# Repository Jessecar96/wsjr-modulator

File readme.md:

# The Weather STAR Revamped

This project is an update to https://github.com/thetechknight/wsjr-modulator that replaces the Arduino Mega, with a Reaspberry Pi Zero. This allows you to write a data sending solution on device instead of requiring a connection to another computer or server for data.

The `schematic` folder contains the updated schematic and board layout files in KiCad 8. 
`schematic_orig` contains thetechknight's original EAGLE cad schematic.
`code` contains code written for the Arduino based board written for  BASCOM-AVR.

The software that runs on the Raspberry Pi can be found here: https://github.com/Jessecar96/wsjr-data-encoder

License: https://creativecommons.org/licenses/by-nc-sa/4.0/

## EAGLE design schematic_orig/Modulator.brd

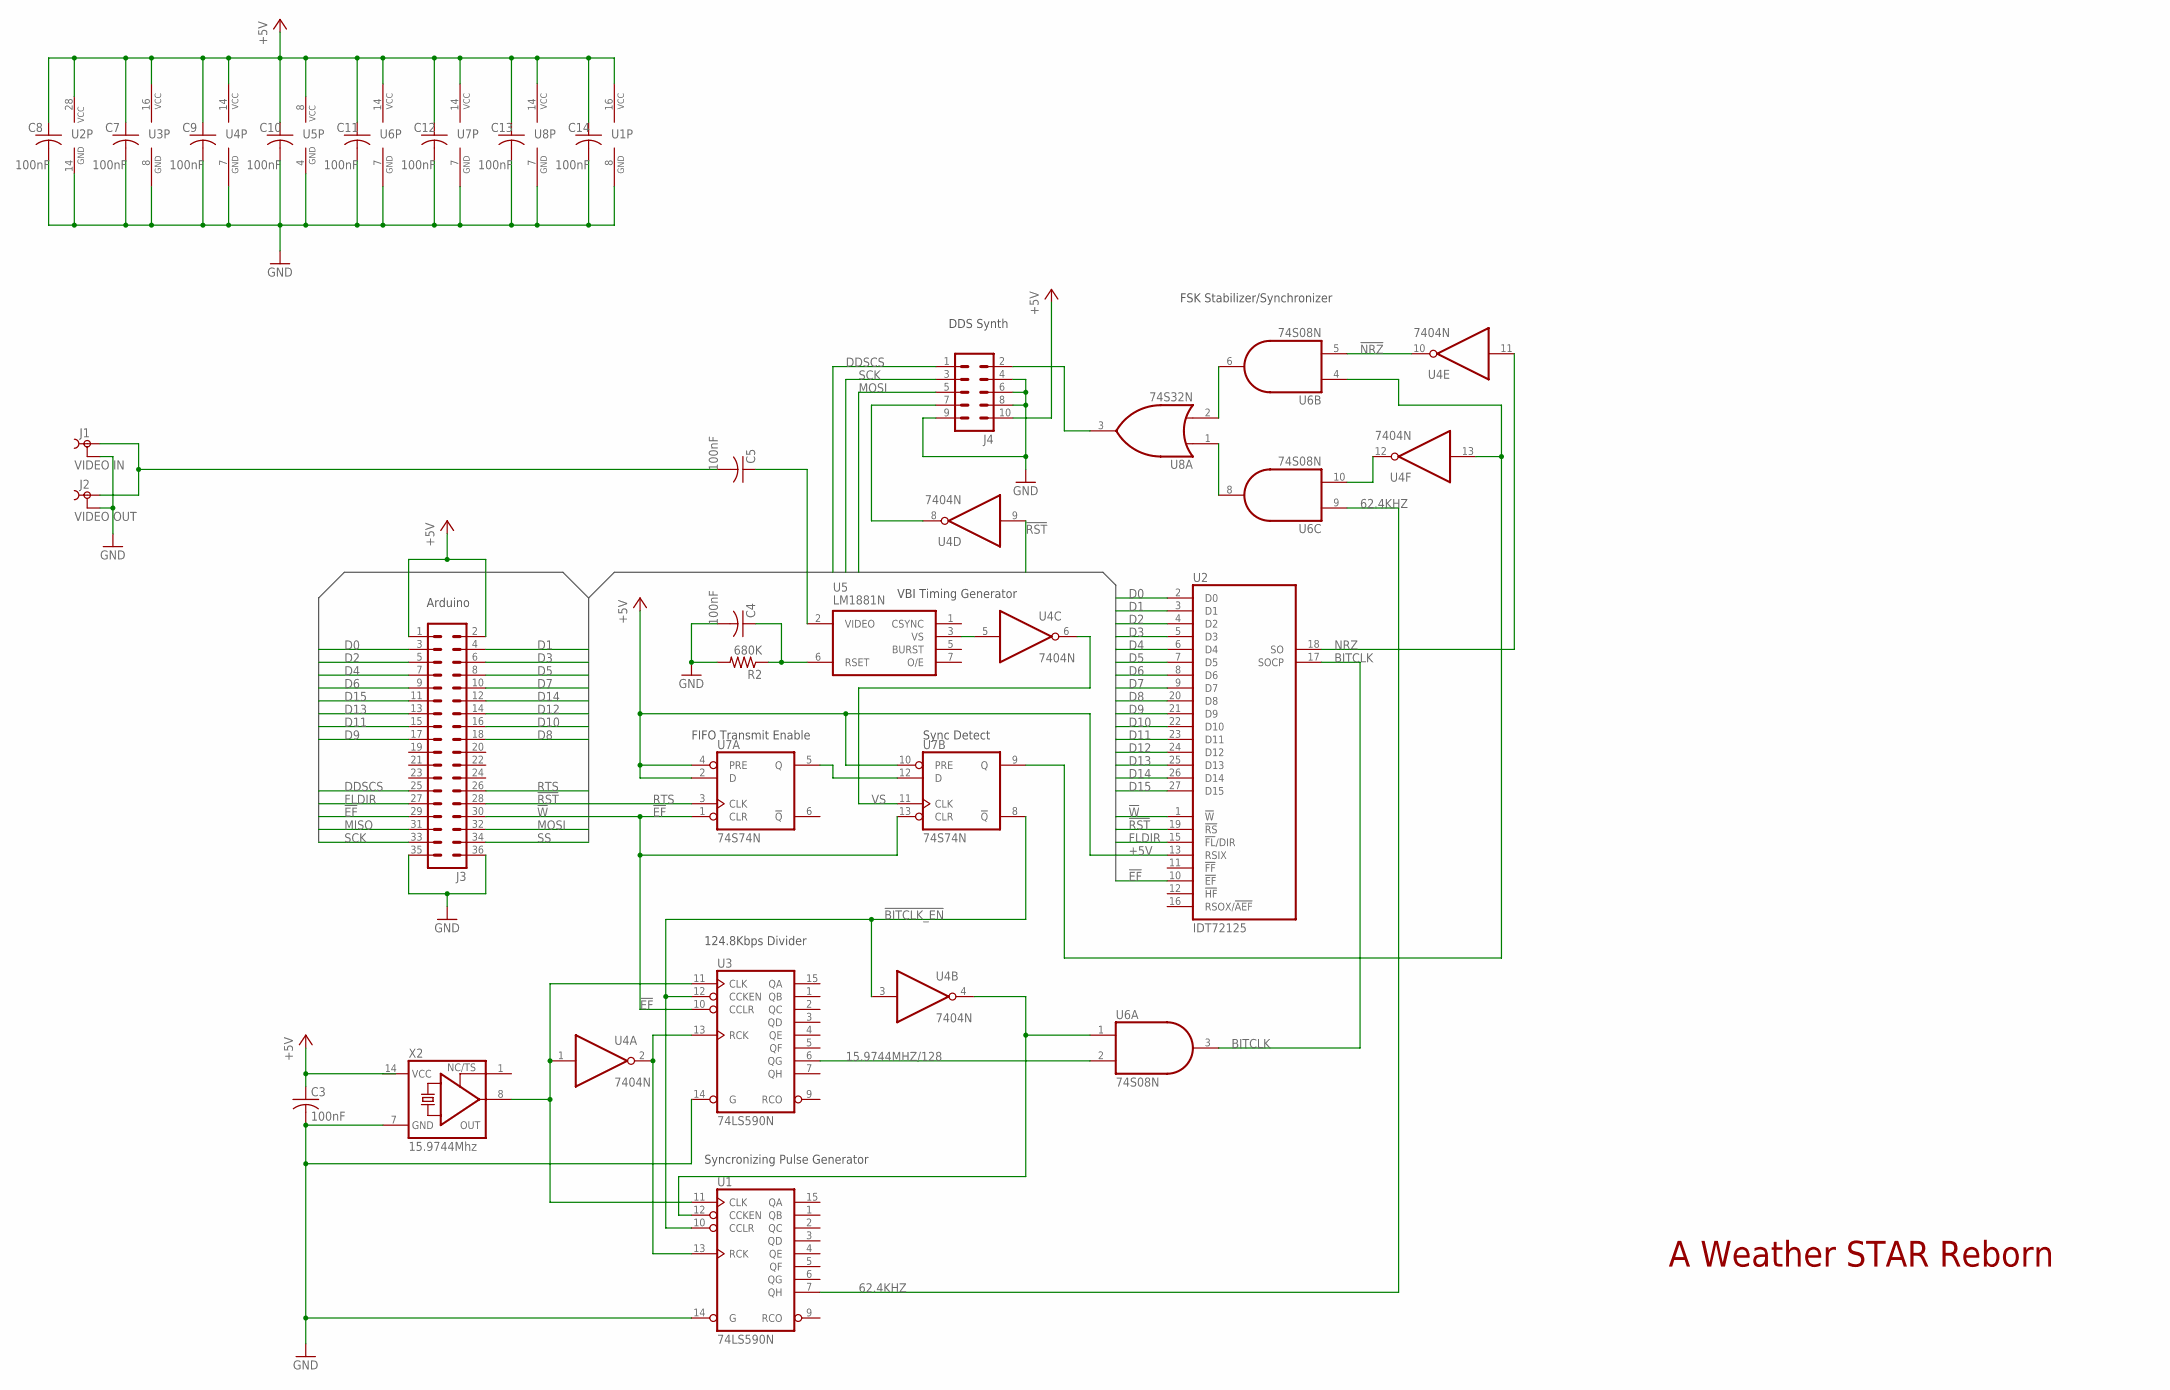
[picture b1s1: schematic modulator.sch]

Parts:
C3, C4, C5, C7, C8, C9, C10, C11, C12, C13, C14: 100nF; C050-025X075
J1: VIDEO IN; TOBU3
J2: VIDEO OUT; TOBU3
J3: MA18-2
J4: MA05-2
R2: 680K; 0207/12
U1, U3: 74LS590N; DIL16
U2: IDT72125; SO28L
U4: 7404N; DIL14
U5: LM1881N; DIL08
U6: 74S08N; DIL14
U7: 74S74N; DIL14
U8: 74S32N; DIL14
X2: 15.9744Mhz; DIL14S

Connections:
15.9744MHZ/128: U3.6 (QG), U6.2 (I1)
62.4KHZ: U1.7 (QH), U6.9 (I0)
!BITCLK_EN: U1.10 (CCLR), U3.12 (CCKEN), U4.3 (I), U7.8 (!Q)
!EF: J3.29, U2.10 (!EF), U3.10 (CCLR), U7.1 (CLR), U7.13 (CLR)
!NRZ: U4.10 (O), U6.5 (I1)
!RST: J3.28, U2.19 (!RS), U4.9 (I)
!W: J3.30, U2.1 (!W)
+5V: C3.1, C7.1, C8.1, C9.1, C10.1, C11.1, C12.1, C13.1, C14.1, J3.1, J3.2, J4.10, U1.16 (VCC), U2.13 (RSIX), U2.28 (VCC), U3.16 (VCC), U4.14 (VCC), U5.8 (VCC), U6.14 (VCC), U7.2 (D), U7.4 (PRE), U7.10 (PRE), U7.14 (VCC), U8.14 (VCC), X2.14 (VCC)
BITCLK: U2.17 (SOCP), U6.3 (O)
D0: J3.3, U2.2 (D0)
D1: J3.4, U2.3 (D1)
D2: J3.5, U2.4 (D2)
D3: J3.6, U2.5 (D3)
D4: J3.7, U2.6 (D4)
D5: J3.8, U2.7 (D5)
D6: J3.9, U2.8 (D6)
D7: J3.10, U2.9 (D7)
D8: J3.18, U2.20 (D8)
D9: J3.17, U2.21 (D9)
D10: J3.16, U2.22 (D10)
D11: J3.15, U2.23 (D11)
D12: J3.14, U2.24 (D12)
D13: J3.13, U2.25 (D13)
D14: J3.12, U2.26 (D14)
D15: J3.11, U2.27 (D15)
DDSCS: J3.25, J4.1
FLDIR: J3.27, U2.15 (!FL!/DIR)
GND: C3.2, C4.2, C7.2, C8.2, C9.2, C10.2, C11.2, C12.2, C13.2, C14.2, J1.2, J1.2@1 (2), J1.2@2 (2), J2.2, J2.2@1 (2), J2.2@2 (2), J3.35, J3.36, J4.4, J4.6, J4.8, J4.9, R2.2, U1.8 (GND), U1.14 (G), U2.14 (GND), U3.8 (GND), U3.14 (G), U4.7 (GND), U5.4 (GND), U6.7 (GND), U7.7 (GND), U8.7 (GND), X2.7 (GND)
MISO: J3.31
MOSI: J3.32, J4.5
unnamed: J4.7, U4.8 (O)
unnamed: J4.2, U8.3 (O)
unnamed: U1.11 (CLK), U3.11 (CLK), U4.1 (I), X2.8 (OUT)
unnamed: U1.13 (RCK), U3.13 (RCK), U4.2 (O)
unnamed: U1.12 (CCKEN), U4.4 (O), U6.1 (I0)
unnamed: U4.13 (I), U6.4 (I0), U7.9 (Q)
unnamed: C5.2, J1.1, J2.1
unnamed: U7.5 (Q), U7.12 (D)
unnamed: U4.5 (I), U5.3 (VS)
unnamed: U4.12 (O), U6.10 (I1)
unnamed: C4.1, R2.1, U5.6 (RSET)
unnamed: U6.6 (O), U8.2 (I1)
unnamed: C5.1, U5.2 (VIDEO)
unnamed: U6.8 (O), U8.1 (I0)
NRZ: U2.18 (SO), U4.11 (I)
RTS: J3.26, U7.3 (CLK)
SCK: J3.33, J4.3
SS: J3.34
VS: U4.6 (O), U7.11 (CLK)

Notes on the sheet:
A Weather STAR Reborn
124.8Kbps Divider
FIFO Transmit Enable
Sync Detect
VBI Timing Generator
Arduino
DDS Synth
FSK Stabilizer/Synchronizer
Syncronizing Pulse Generator

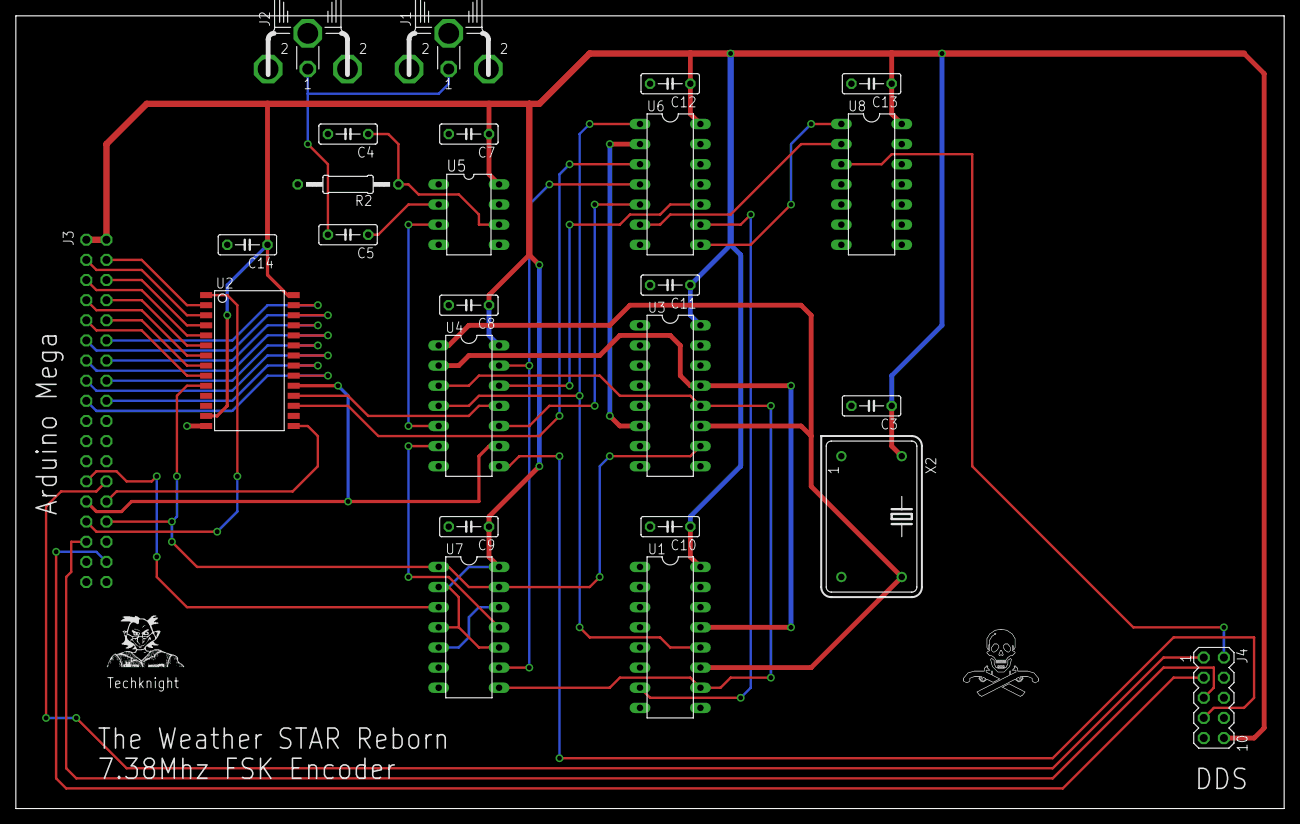
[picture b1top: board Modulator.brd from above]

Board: 2 copper layers, 160.0 x 100.0 mm, 27 parts (1 on the bottom side), 47 nets.

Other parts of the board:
U$1: LOGO
U$2: JOLLYROGER

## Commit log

2024-10-31 Add board layout
2024-10-31 Added images
2024-12-17 First draft of new circuit with raspberry pi
2024-12-17 Fix ground on top of bus
2024-12-20 First draft of PCB routing
2024-12-20 Make room for SMA connectors on DDS board
2024-12-21 Add decoupling capacitors to level shifters
2024-12-22 Change some decoupling capacitors, and usb-c resistors to SMT
2024-12-22 Update capacitor footprints
2024-12-22 Slight cleanup
2024-12-23 Add holes for case
2024-12-31 Update label placement
2024-12-31 Fix another label placement
2025-12-04 Add link to software source
